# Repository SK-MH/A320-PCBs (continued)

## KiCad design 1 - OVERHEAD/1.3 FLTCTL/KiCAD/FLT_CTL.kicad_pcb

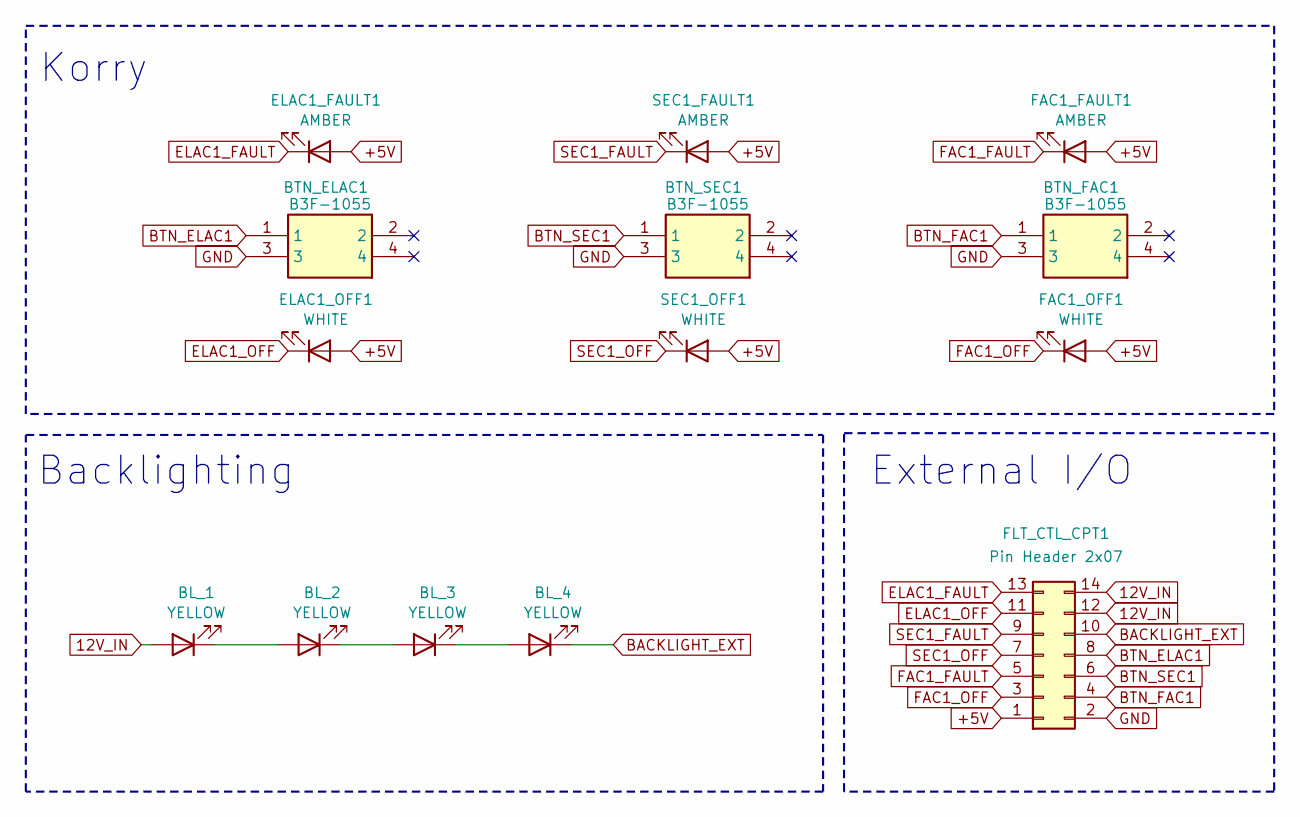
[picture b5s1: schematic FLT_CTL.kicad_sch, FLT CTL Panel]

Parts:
BL_1, BL_2, BL_3, BL_4: YELLOW; LED_D3.0mm
BTN_ELAC1: B3F-1055; B3F1000; Mouser Part Number 653-B3F-1055
BTN_FAC1: B3F-1055; B3F1000; Mouser Part Number 653-B3F-1055
BTN_SEC1: B3F-1055; B3F1000; Mouser Part Number 653-B3F-1055
ELAC1_FAULT1: AMBER; LED_D3.0mm
ELAC1_OFF1: WHITE; LED_D3.0mm
FAC1_FAULT1: AMBER; LED_D3.0mm
FAC1_OFF1: WHITE; LED_D3.0mm
FLT_CTL_CPT1: Pin Header 2x07; IDC-Header_2x07_P2.54mm_Vertical
SEC1_FAULT1: AMBER; LED_D3.0mm
SEC1_OFF1: WHITE; LED_D3.0mm

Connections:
12V_IN: BL_1.2 (A), FLT_CTL_CPT1.12, FLT_CTL_CPT1.14
+5V: ELAC1_FAULT1.2 (A), ELAC1_OFF1.2 (A), FAC1_FAULT1.2 (A), FAC1_OFF1.2 (A), FLT_CTL_CPT1.1, SEC1_FAULT1.2 (A), SEC1_OFF1.2 (A)
BACKLIGHT_EXT: BL_4.1 (K), FLT_CTL_CPT1.10
BTN_ELAC1: BTN_ELAC1.1, FLT_CTL_CPT1.8
BTN_FAC1: BTN_FAC1.1, FLT_CTL_CPT1.4
BTN_SEC1: BTN_SEC1.1, FLT_CTL_CPT1.6
ELAC1_FAULT: ELAC1_FAULT1.1 (K), FLT_CTL_CPT1.13
ELAC1_OFF: ELAC1_OFF1.1 (K), FLT_CTL_CPT1.11
FAC1_FAULT: FAC1_FAULT1.1 (K), FLT_CTL_CPT1.5
FAC1_OFF: FAC1_OFF1.1 (K), FLT_CTL_CPT1.3
GND: BTN_ELAC1.3, BTN_FAC1.3, BTN_SEC1.3, FLT_CTL_CPT1.2
unnamed: BL_1.1 (K), BL_2.2 (A)
unnamed: BL_2.1 (K), BL_3.2 (A)
unnamed: BL_3.1 (K), BL_4.2 (A)
SEC1_FAULT: FLT_CTL_CPT1.9, SEC1_FAULT1.1 (K)
SEC1_OFF: FLT_CTL_CPT1.7, SEC1_OFF1.1 (K)

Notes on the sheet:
Backlighting
External I/O
Korry

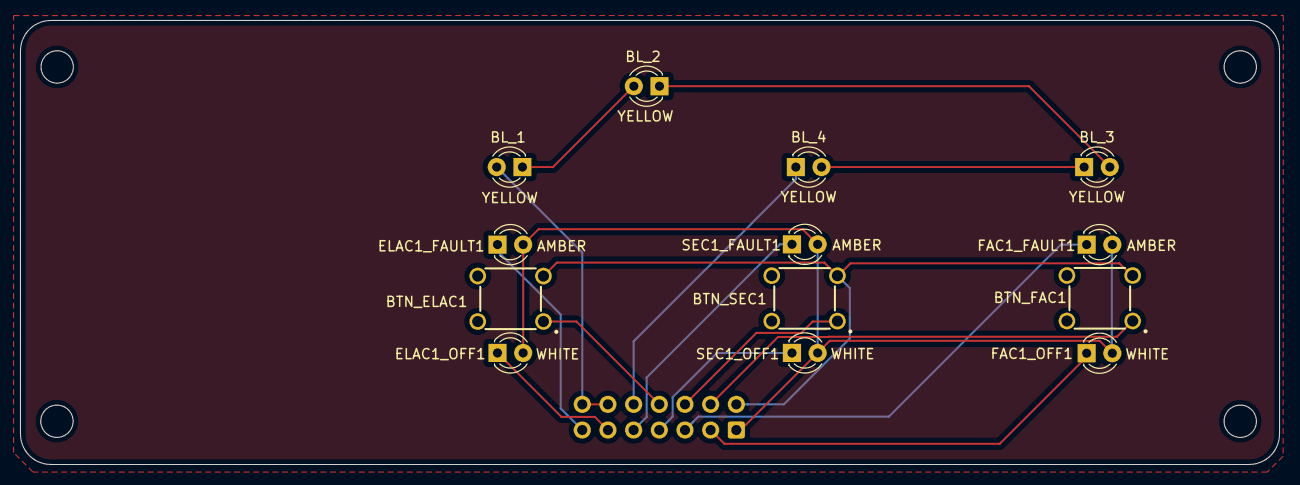
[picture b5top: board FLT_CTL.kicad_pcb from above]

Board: 2 copper layers, 124.6 x 43.9 mm, 14 parts (1 on the bottom side), 16 nets.

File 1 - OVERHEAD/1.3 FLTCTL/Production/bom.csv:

Designator,Footprint,Quantity,Value,LCSC Part #
"BL_1, BL_2, BL_3, BL_4",LED_D3.0mm,4,YELLOW,
"BTN_ELAC1, BTN_FAC1, BTN_SEC1",B3F1000,3,B3F-1055,
"ELAC1_FAULT1, FAC1_FAULT1, SEC1_FAULT1",LED_D3.0mm,3,AMBER,
"ELAC1_OFF1, FAC1_OFF1, SEC1_OFF1",LED_D3.0mm,3,WHITE,
FLT_CTL_CPT1,IDC-Header_2x07_P2.54mm_Vertical,1,Pin Header 2x07,

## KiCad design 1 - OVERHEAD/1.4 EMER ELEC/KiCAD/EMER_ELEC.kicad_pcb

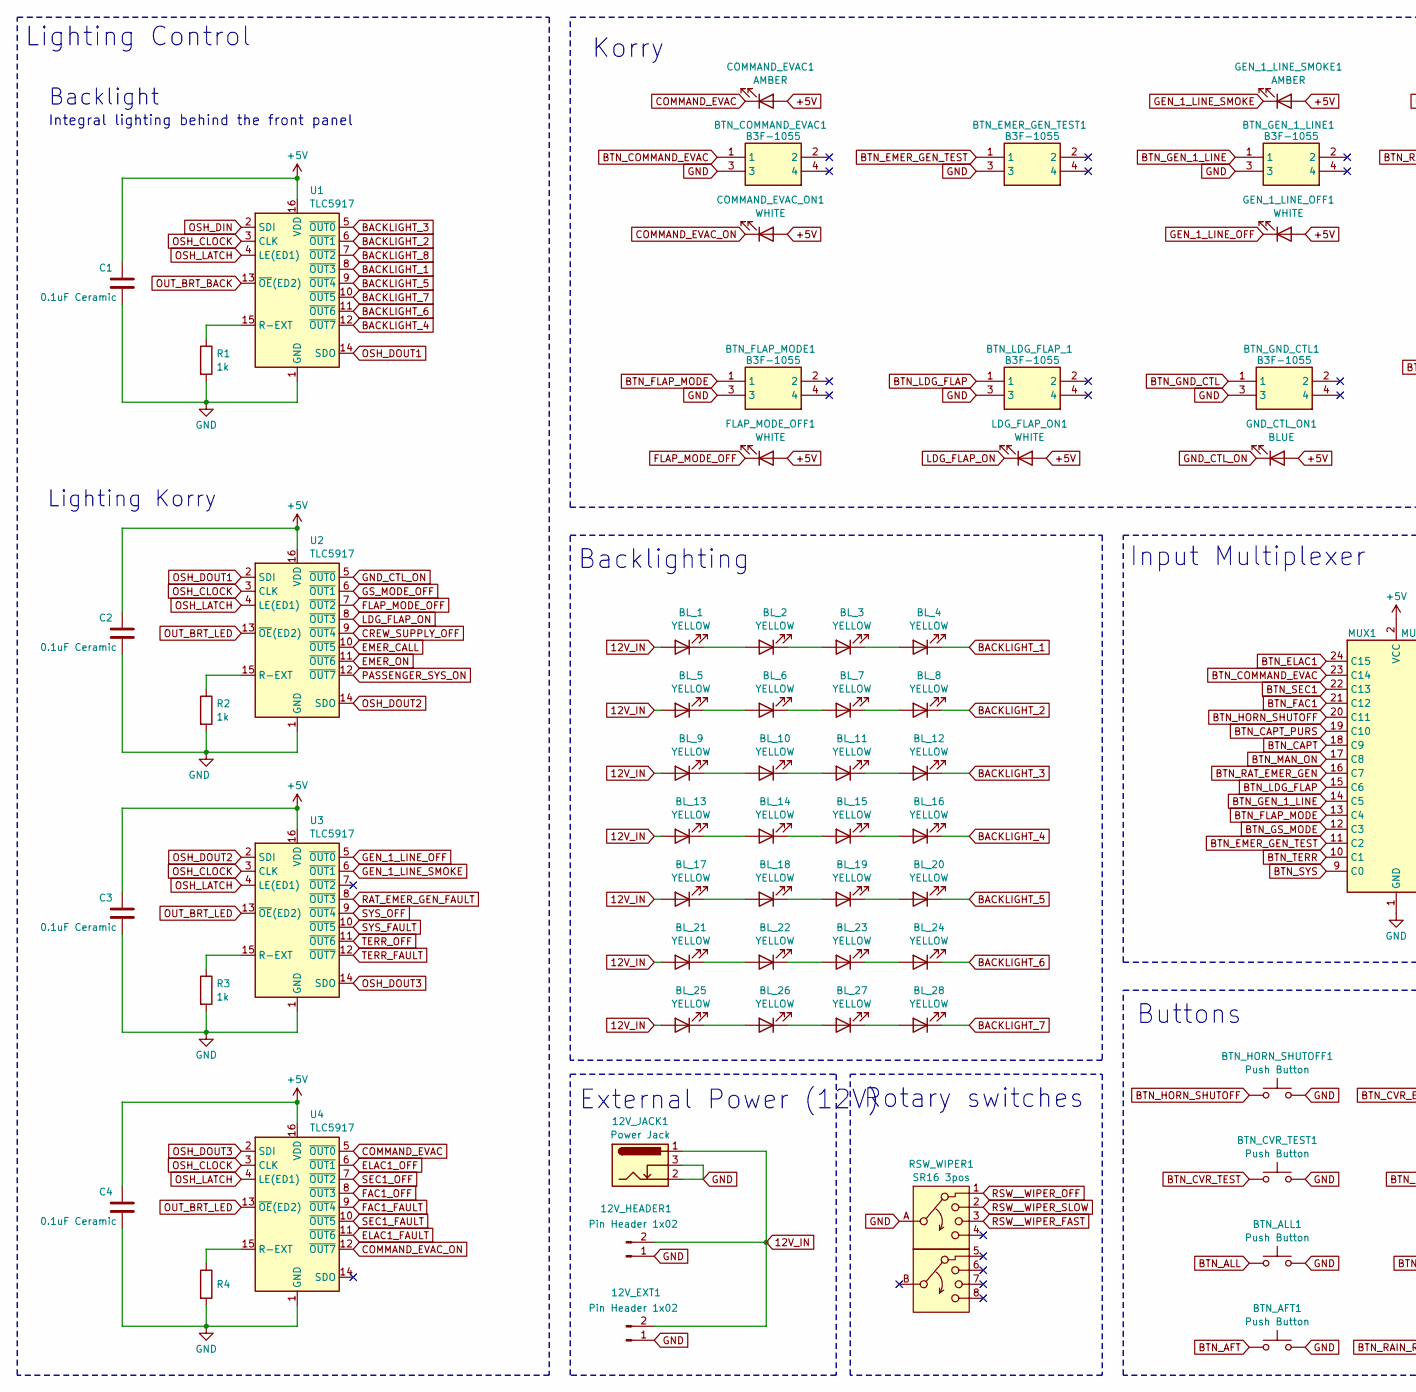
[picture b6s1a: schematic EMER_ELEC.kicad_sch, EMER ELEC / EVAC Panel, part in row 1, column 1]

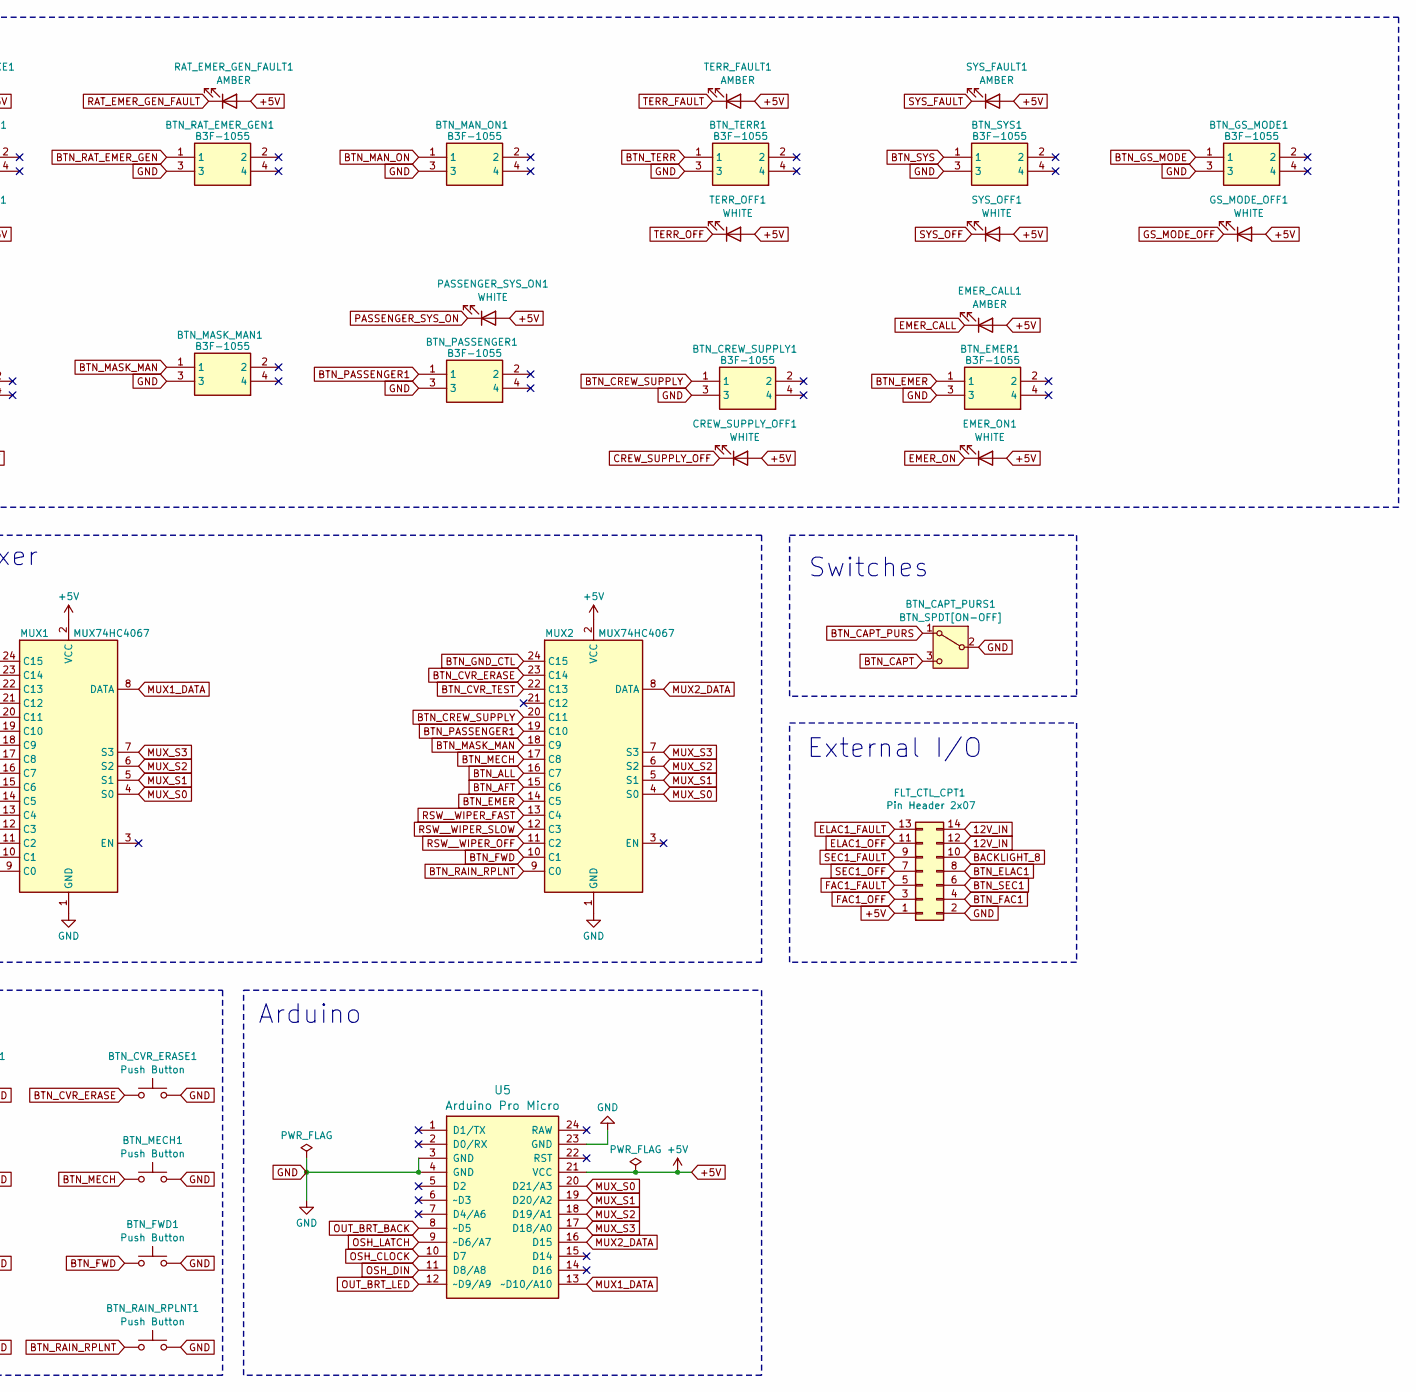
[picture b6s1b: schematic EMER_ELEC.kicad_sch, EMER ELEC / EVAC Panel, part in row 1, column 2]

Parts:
12V_EXT1, 12V_HEADER1: Pin Header 1x02; JST_EH_B2B-EH-A_1x02_P2.50mm_Vertical
12V_JACK1: Power Jack; BarrelJack_Horizontal
BL_1, BL_2, BL_3, BL_4, BL_5, BL_6, BL_7, BL_8, BL_9, BL_10, BL_11, BL_12, BL_13, BL_14, BL_15, BL_16, BL_17, BL_18, BL_19, BL_20, BL_21, BL_22, BL_23, BL_24, BL_25, BL_26, BL_27, BL_28: YELLOW; LED_D3.0mm
BTN_AFT1: Push Button; SW-Push
BTN_ALL1: Push Button; SW-Push
BTN_CAPT_PURS1: BTN_SPDT[ON-OFF]; T80-Z1
BTN_COMMAND_EVAC1: B3F-1055; B3F1000; Mouser Part Number 653-B3F-1055
BTN_CREW_SUPPLY1: B3F-1055; B3F1000; Mouser Part Number 653-B3F-1055
BTN_CVR_ERASE1: Push Button; SW-Push
BTN_CVR_TEST1: Push Button; SW-Push
BTN_EMER1: B3F-1055; B3F1000; Mouser Part Number 653-B3F-1055
BTN_EMER_GEN_TEST1: B3F-1055; B3F1000; Mouser Part Number 653-B3F-1055
BTN_FLAP_MODE1: B3F-1055; B3F1000; Mouser Part Number 653-B3F-1055
BTN_FWD1: Push Button; SW-Push
BTN_GEN_1_LINE1: B3F-1055; B3F1000; Mouser Part Number 653-B3F-1055
BTN_GND_CTL1: B3F-1055; B3F1000; Mouser Part Number 653-B3F-1055
BTN_GS_MODE1: B3F-1055; B3F1000; Mouser Part Number 653-B3F-1055
BTN_HORN_SHUTOFF1: Push Button; SW-Push
BTN_LDG_FLAP_1: B3F-1055; B3F1000; Mouser Part Number 653-B3F-1055
BTN_MAN_ON1: B3F-1055; B3F1000; Mouser Part Number 653-B3F-1055
BTN_MASK_MAN1: B3F-1055; B3F1000; Mouser Part Number 653-B3F-1055
BTN_MECH1: Push Button; SW-Push
BTN_PASSENGER1: B3F-1055; B3F1000; Mouser Part Number 653-B3F-1055
BTN_RAIN_RPLNT1: Push Button; SW-Push
BTN_RAT_EMER_GEN1: B3F-1055; B3F1000; Mouser Part Number 653-B3F-1055
BTN_SYS1: B3F-1055; B3F1000; Mouser Part Number 653-B3F-1055
BTN_TERR1: B3F-1055; B3F1000; Mouser Part Number 653-B3F-1055
C1, C2, C3, C4: 0.1uF Ceramic; C_Disc_D3.0mm_W1.6mm_P2.50mm
COMMAND_EVAC1: AMBER; LED_D3.0mm
COMMAND_EVAC_ON1: WHITE; LED_D3.0mm
CREW_SUPPLY_OFF1: WHITE; LED_D3.0mm
EMER_CALL1: AMBER; LED_D3.0mm
EMER_ON1: WHITE; LED_D3.0mm
FLAP_MODE_OFF1: WHITE; LED_D3.0mm
FLT_CTL_CPT1: Pin Header 2x07; IDC-Header_2x07_P2.54mm_Vertical
GEN_1_LINE_OFF1: WHITE; LED_D3.0mm
GEN_1_LINE_SMOKE1: AMBER; LED_D3.0mm
GND_CTL_ON1: BLUE; LED_D3.0mm
GS_MODE_OFF1: WHITE; LED_D3.0mm
LDG_FLAP_ON1: WHITE; LED_D3.0mm
MUX1, MUX2: MUX74HC4067
PASSENGER_SYS_ON1: WHITE; LED_D3.0mm
R1, R2, R3, R4: 1k; R_Axial_DIN0204_L3.6mm_D1.6mm_P7.62mm_Horizontal
RAT_EMER_GEN_FAULT1: AMBER; LED_D3.0mm
RSW_WIPER1: SR16 3pos; SR16-AB
SYS_FAULT1: AMBER; LED_D3.0mm
SYS_OFF1: WHITE; LED_D3.0mm
TERR_FAULT1: AMBER; LED_D3.0mm
TERR_OFF1: WHITE; LED_D3.0mm
U1, U2, U3, U4: TLC5917; DIP-16_W7.62mm
U5: Arduino Pro Micro; Sparkfun_Pro_Micro

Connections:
12V_IN: 12V_EXT1.2, 12V_HEADER1.2, 12V_JACK1.1, BL_1.2 (A), BL_5.2 (A), BL_9.2 (A), BL_13.2 (A), BL_17.2 (A), BL_21.2 (A), BL_25.2 (A), FLT_CTL_CPT1.12, FLT_CTL_CPT1.14
+5V: C1.1, C2.1, C3.1, C4.1, COMMAND_EVAC1.2 (A), COMMAND_EVAC_ON1.2 (A), CREW_SUPPLY_OFF1.2 (A), EMER_CALL1.2 (A), EMER_ON1.2 (A), FLAP_MODE_OFF1.2 (A), FLT_CTL_CPT1.1, GEN_1_LINE_OFF1.2 (A), GEN_1_LINE_SMOKE1.2 (A), GND_CTL_ON1.2 (A), GS_MODE_OFF1.2 (A), LDG_FLAP_ON1.2 (A), MUX1.2 (VCC), MUX2.2 (VCC), PASSENGER_SYS_ON1.2 (A), RAT_EMER_GEN_FAULT1.2 (A), SYS_FAULT1.2 (A), SYS_OFF1.2 (A), TERR_FAULT1.2 (A), TERR_OFF1.2 (A), U1.16 (VDD), U2.16 (VDD), U3.16 (VDD), U4.16 (VDD), U5.21 (VCC)
BACKLIGHT_1: BL_4.1 (K), U1.8 (~OUT3)
BACKLIGHT_2: BL_8.1 (K), U1.6 (~OUT1)
BACKLIGHT_3: BL_12.1 (K), U1.5 (~OUT0)
BACKLIGHT_4: BL_16.1 (K), U1.12 (~OUT7)
BACKLIGHT_5: BL_20.1 (K), U1.9 (~OUT4)
BACKLIGHT_6: BL_24.1 (K), U1.11 (~OUT6)
BACKLIGHT_7: BL_28.1 (K), U1.10 (~OUT5)
BACKLIGHT_8: FLT_CTL_CPT1.10, U1.7 (~OUT2)
BTN_AFT: BTN_AFT1.1, MUX2.15 (C6)
BTN_ALL: BTN_ALL1.1, MUX2.16 (C7)
BTN_CAPT: BTN_CAPT_PURS1.3 (C), MUX1.18 (C9)
BTN_CAPT_PURS: BTN_CAPT_PURS1.1 (A), MUX1.19 (C10)
BTN_COMMAND_EVAC: BTN_COMMAND_EVAC1.1, MUX1.23 (C14)
BTN_CREW_SUPPLY: BTN_CREW_SUPPLY1.1, MUX2.20 (C11)
BTN_CVR_ERASE: BTN_CVR_ERASE1.1, MUX2.23 (C14)
BTN_CVR_TEST: BTN_CVR_TEST1.1, MUX2.22 (C13)
BTN_ELAC1: FLT_CTL_CPT1.8, MUX1.24 (C15)
BTN_EMER: BTN_EMER1.1, MUX2.14 (C5)
BTN_EMER_GEN_TEST: BTN_EMER_GEN_TEST1.1, MUX1.11 (C2)
BTN_FAC1: FLT_CTL_CPT1.4, MUX1.21 (C12)
BTN_FLAP_MODE: BTN_FLAP_MODE1.1, MUX1.13 (C4)
BTN_FWD: BTN_FWD1.1, MUX2.10 (C1)
BTN_GEN_1_LINE: BTN_GEN_1_LINE1.1, MUX1.14 (C5)
BTN_GND_CTL: BTN_GND_CTL1.1, MUX2.24 (C15)
BTN_GS_MODE: BTN_GS_MODE1.1, MUX1.12 (C3)
BTN_HORN_SHUTOFF: BTN_HORN_SHUTOFF1.1, MUX1.20 (C11)
BTN_LDG_FLAP: BTN_LDG_FLAP_1.1, MUX1.15 (C6)
BTN_MAN_ON: BTN_MAN_ON1.1, MUX1.17 (C8)
BTN_MASK_MAN: BTN_MASK_MAN1.1, MUX2.18 (C9)
BTN_MECH: BTN_MECH1.1, MUX2.17 (C8)
BTN_PASSENGER1: BTN_PASSENGER1.1, MUX2.19 (C10)
BTN_RAIN_RPLNT: BTN_RAIN_RPLNT1.1, MUX2.9 (C0)
BTN_RAT_EMER_GEN: BTN_RAT_EMER_GEN1.1, MUX1.16 (C7)
BTN_SEC1: FLT_CTL_CPT1.6, MUX1.22 (C13)
BTN_SYS: BTN_SYS1.1, MUX1.9 (C0)
BTN_TERR: BTN_TERR1.1, MUX1.10 (C1)
COMMAND_EVAC: COMMAND_EVAC1.1 (K), U4.5 (~OUT0)
COMMAND_EVAC_ON: COMMAND_EVAC_ON1.1 (K), U4.12 (~OUT7)
CREW_SUPPLY_OFF: CREW_SUPPLY_OFF1.1 (K), U2.9 (~OUT4)
ELAC1_FAULT: FLT_CTL_CPT1.13, U4.11 (~OUT6)
ELAC1_OFF: FLT_CTL_CPT1.11, U4.6 (~OUT1)
EMER_CALL: EMER_CALL1.1 (K), U2.10 (~OUT5)
EMER_ON: EMER_ON1.1 (K), U2.11 (~OUT6)
FAC1_FAULT: FLT_CTL_CPT1.5, U4.9 (~OUT4)
FAC1_OFF: FLT_CTL_CPT1.3, U4.8 (~OUT3)
FLAP_MODE_OFF: FLAP_MODE_OFF1.1 (K), U2.7 (~OUT2)
GEN_1_LINE_OFF: GEN_1_LINE_OFF1.1 (K), U3.5 (~OUT0)
GEN_1_LINE_SMOKE: GEN_1_LINE_SMOKE1.1 (K), U3.6 (~OUT1)
GND: 12V_EXT1.1, 12V_HEADER1.1, 12V_JACK1.2, 12V_JACK1.3, BTN_AFT1.2, BTN_ALL1.2, BTN_CAPT_PURS1.2 (B), BTN_COMMAND_EVAC1.3, BTN_CREW_SUPPLY1.3, BTN_CVR_ERASE1.2, BTN_CVR_TEST1.2, BTN_EMER1.3, BTN_EMER_GEN_TEST1.3, BTN_FLAP_MODE1.3, BTN_FWD1.2, BTN_GEN_1_LINE1.3, BTN_GND_CTL1.3, BTN_GS_MODE1.3, BTN_HORN_SHUTOFF1.2, BTN_LDG_FLAP_1.3, BTN_MAN_ON1.3, BTN_MASK_MAN1.3, BTN_MECH1.2, BTN_PASSENGER1.3, BTN_RAIN_RPLNT1.2, BTN_RAT_EMER_GEN1.3, BTN_SYS1.3, BTN_TERR1.3, C1.2, C2.2, C3.2, C4.2, FLT_CTL_CPT1.2, MUX1.1 (GND), MUX2.1 (GND), R1.2, R2.2, R3.2, R4.2, RSW_WIPER1.A, U1.1 (GND), U2.1 (GND), U3.1 (GND), U4.1 (GND), U5.3 (GND), U5.4 (GND), U5.23 (GND)
GND_CTL_ON: GND_CTL_ON1.1 (K), U2.5 (~OUT0)
GS_MODE_OFF: GS_MODE_OFF1.1 (K), U2.6 (~OUT1)
LDG_FLAP_ON: LDG_FLAP_ON1.1 (K), U2.8 (~OUT3)
MUX1_DATA: MUX1.8 (DATA), U5.13 (~D10/A10)
MUX2_DATA: MUX2.8 (DATA), U5.16 (D15)
MUX_S0: MUX1.4 (S0), MUX2.4 (S0), U5.20 (D21/A3)
MUX_S1: MUX1.5 (S1), MUX2.5 (S1), U5.19 (D20/A2)
MUX_S2: MUX1.6 (S2), MUX2.6 (S2), U5.18 (D19/A1)
MUX_S3: MUX1.7 (S3), MUX2.7 (S3), U5.17 (D18/A0)
unnamed: BL_1.1 (K), BL_2.2 (A)
unnamed: BL_2.1 (K), BL_3.2 (A)
unnamed: BL_3.1 (K), BL_4.2 (A)
unnamed: BL_5.1 (K), BL_6.2 (A)
unnamed: BL_6.1 (K), BL_7.2 (A)
unnamed: BL_7.1 (K), BL_8.2 (A)
unnamed: BL_9.1 (K), BL_10.2 (A)
unnamed: BL_10.1 (K), BL_11.2 (A)
unnamed: BL_11.1 (K), BL_12.2 (A)
unnamed: BL_13.1 (K), BL_14.2 (A)
unnamed: BL_14.1 (K), BL_15.2 (A)
unnamed: BL_15.1 (K), BL_16.2 (A)
unnamed: BL_17.1 (K), BL_18.2 (A)
unnamed: BL_18.1 (K), BL_19.2 (A)
unnamed: BL_19.1 (K), BL_20.2 (A)
unnamed: BL_21.1 (K), BL_22.2 (A)
unnamed: BL_22.1 (K), BL_23.2 (A)
unnamed: BL_23.1 (K), BL_24.2 (A)
unnamed: BL_25.1 (K), BL_26.2 (A)
unnamed: BL_26.1 (K), BL_27.2 (A)
unnamed: BL_27.1 (K), BL_28.2 (A)
unnamed: R1.1, U1.15 (R-EXT)
unnamed: R2.1, U2.15 (R-EXT)
unnamed: R3.1, U3.15 (R-EXT)
unnamed: R4.1, U4.15 (R-EXT)
OSH_CLOCK: U1.3 (CLK), U2.3 (CLK), U3.3 (CLK), U4.3 (CLK), U5.10 (D7)
OSH_DIN: U1.2 (SDI), U5.11 (D8/A8)
OSH_DOUT1: U1.14 (SDO), U2.2 (SDI)
OSH_DOUT2: U2.14 (SDO), U3.2 (SDI)
OSH_DOUT3: U3.14 (SDO), U4.2 (SDI)
OSH_LATCH: U1.4 (LE(ED1)), U2.4 (LE(ED1)), U3.4 (LE(ED1)), U4.4 (LE(ED1)), U5.9 (~D6/A7)
OUT_BRT_BACK: U1.13 (~OE(ED2)), U5.8 (~D5)
OUT_BRT_LED: U2.13 (~OE(ED2)), U3.13 (~OE(ED2)), U4.13 (~OE(ED2)), U5.12 (~D9/A9)
PASSENGER_SYS_ON: PASSENGER_SYS_ON1.1 (K), U2.12 (~OUT7)
RAT_EMER_GEN_FAULT: RAT_EMER_GEN_FAULT1.1 (K), U3.8 (~OUT3)
RSW__WIPER_FAST: MUX2.13 (C4), RSW_WIPER1.3
RSW__WIPER_OFF: MUX2.11 (C2), RSW_WIPER1.1
RSW__WIPER_SLOW: MUX2.12 (C3), RSW_WIPER1.2
SEC1_FAULT: FLT_CTL_CPT1.9, U4.10 (~OUT5)
SEC1_OFF: FLT_CTL_CPT1.7, U4.7 (~OUT2)
SYS_FAULT: SYS_FAULT1.1 (K), U3.10 (~OUT5)
SYS_OFF: SYS_OFF1.1 (K), U3.9 (~OUT4)
TERR_FAULT: TERR_FAULT1.1 (K), U3.12 (~OUT7)
TERR_OFF: TERR_OFF1.1 (K), U3.11 (~OUT6)

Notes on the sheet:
Backlighting
Arduino
Rotary switches
Switches
External I/O
Korry
Input Multiplexer
Buttons
External Power (12V)
Lighting Korry
Lighting Control
Integral lighting behind the front panel
Backlight

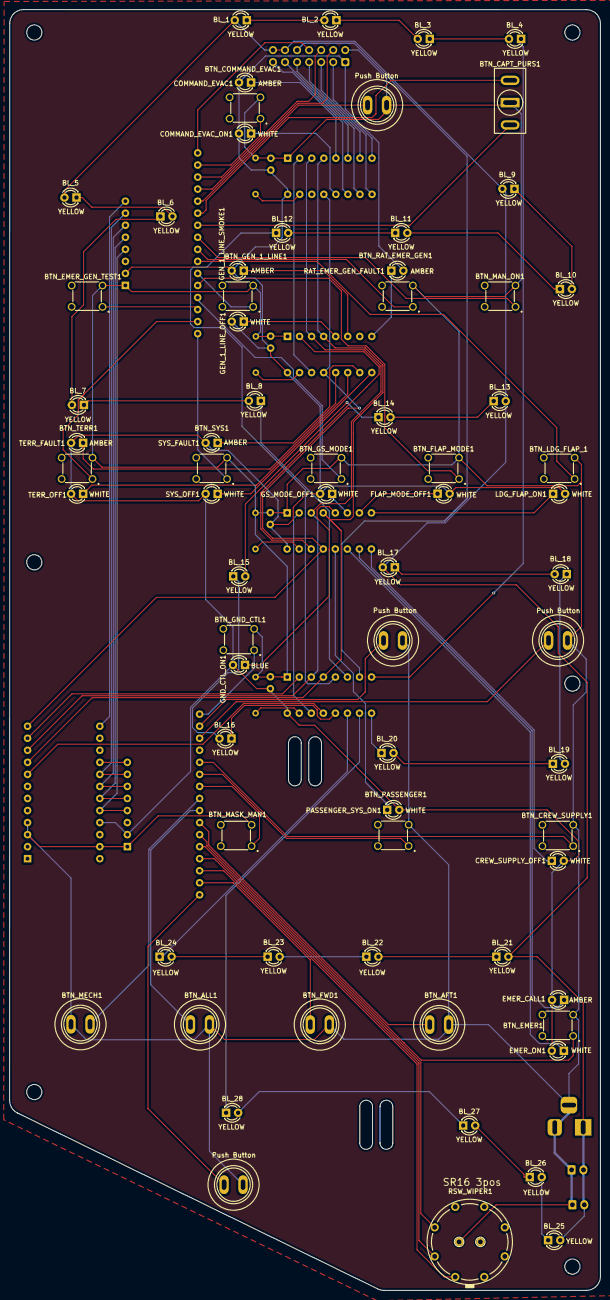
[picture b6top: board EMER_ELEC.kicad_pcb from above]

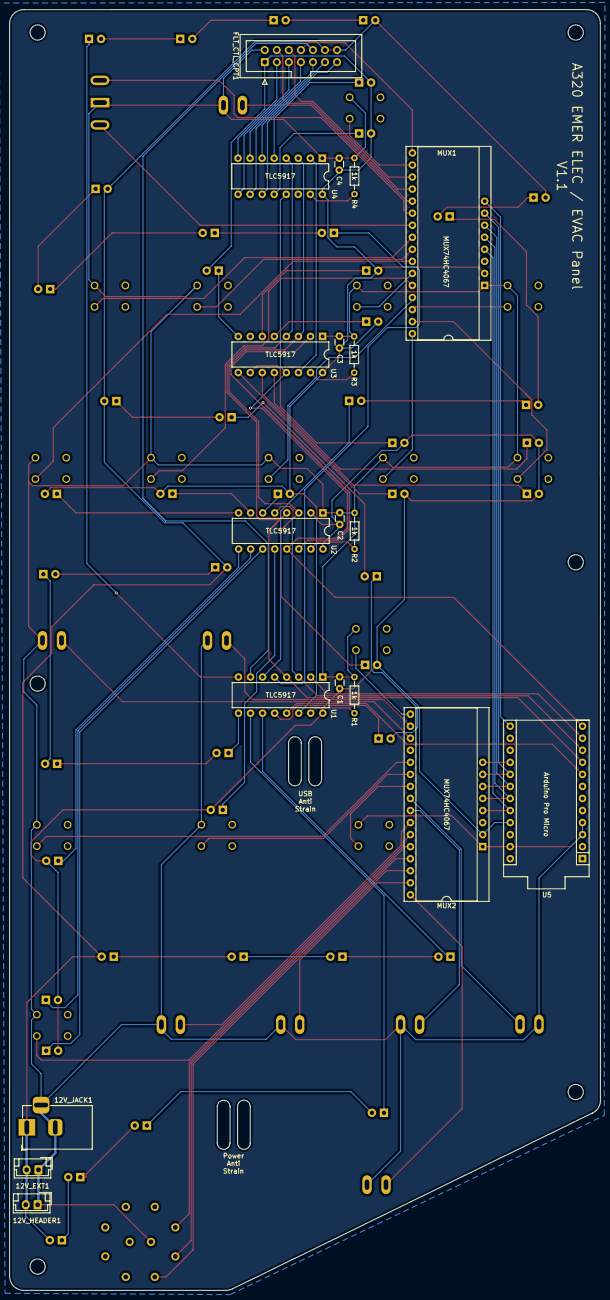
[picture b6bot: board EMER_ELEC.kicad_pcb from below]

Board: 2 copper layers, 124.6 x 270.1 mm, 89 parts (19 on the bottom side), 104 nets.

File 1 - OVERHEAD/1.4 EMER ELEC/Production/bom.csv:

Designator,Footprint,Quantity,Value,LCSC Part #
"12V_EXT1, 12V_HEADER1",JST_EH_B2B-EH-A_1x02_P2.50mm_Vertical,2,Pin Header 1x02,
12V_JACK1,BarrelJack_Horizontal,1,Power Jack,
"BL_1, BL_10, BL_11, BL_12, BL_13, BL_14, BL_15, BL_16, BL_17, BL_18, BL_19, BL_2, BL_20, BL_21, BL_22, BL_23, BL_24, BL_25, BL_26, BL_27, BL_28, BL_3, BL_4, BL_5, BL_6, BL_7, BL_8, BL_9",LED_D3.0mm,28,YELLOW,
"BTN_AFT1, BTN_ALL1, BTN_CVR_ERASE1, BTN_CVR_TEST1, BTN_FWD1, BTN_HORN_SHUTOFF1, BTN_MECH1, BTN_RAIN_RPLNT1",SW-Push,8,Push Button,
BTN_CAPT_PURS1,T80-Z1,1,BTN_SPDT[ON-OFF],
"BTN_COMMAND_EVAC1, BTN_CREW_SUPPLY1, BTN_EMER1, BTN_EMER_GEN_TEST1, BTN_FLAP_MODE1, BTN_GEN_1_LINE1, BTN_GND_CTL1, BTN_GS_MODE1, BTN_LDG_FLAP_1, BTN_MAN_ON1, BTN_MASK_MAN1, BTN_PASSENGER1, BTN_RAT_EMER_GEN1, BTN_SYS1, BTN_TERR1",B3F1000,15,B3F-1055,
"C1, C2, C3, C4",C_Disc_D3.0mm_W1.6mm_P2.50mm,4,0.1uF Ceramic,
"COMMAND_EVAC1, EMER_CALL1, GEN_1_LINE_SMOKE1, RAT_EMER_GEN_FAULT1, SYS_FAULT1, TERR_FAULT1",LED_D3.0mm,6,AMBER,
"COMMAND_EVAC_ON1, CREW_SUPPLY_OFF1, EMER_ON1, FLAP_MODE_OFF1, GEN_1_LINE_OFF1, GS_MODE_OFF1, LDG_FLAP_ON1, PASSENGER_SYS_ON1, SYS_OFF1, TERR_OFF1",LED_D3.0mm,10,WHITE,
FLT_CTL_CPT1,IDC-Header_2x07_P2.54mm_Vertical,1,Pin Header 2x07,
GND_CTL_ON1,LED_D3.0mm,1,BLUE,
"MUX1, MUX2",MUX74HC4067,2,MUX74HC4067,
"R1, R2, R3, R4",R_Axial_DIN0204_L3.6mm_D1.6mm_P7.62mm_Horizontal,4,1k,
RSW_WIPER1,SR16-AB,1,SR16 3pos,
"U1, U2, U3, U4",DIP-16_W7.62mm,4,TLC5917,
U5,Sparkfun_Pro_Micro,1,Arduino Pro Micro,

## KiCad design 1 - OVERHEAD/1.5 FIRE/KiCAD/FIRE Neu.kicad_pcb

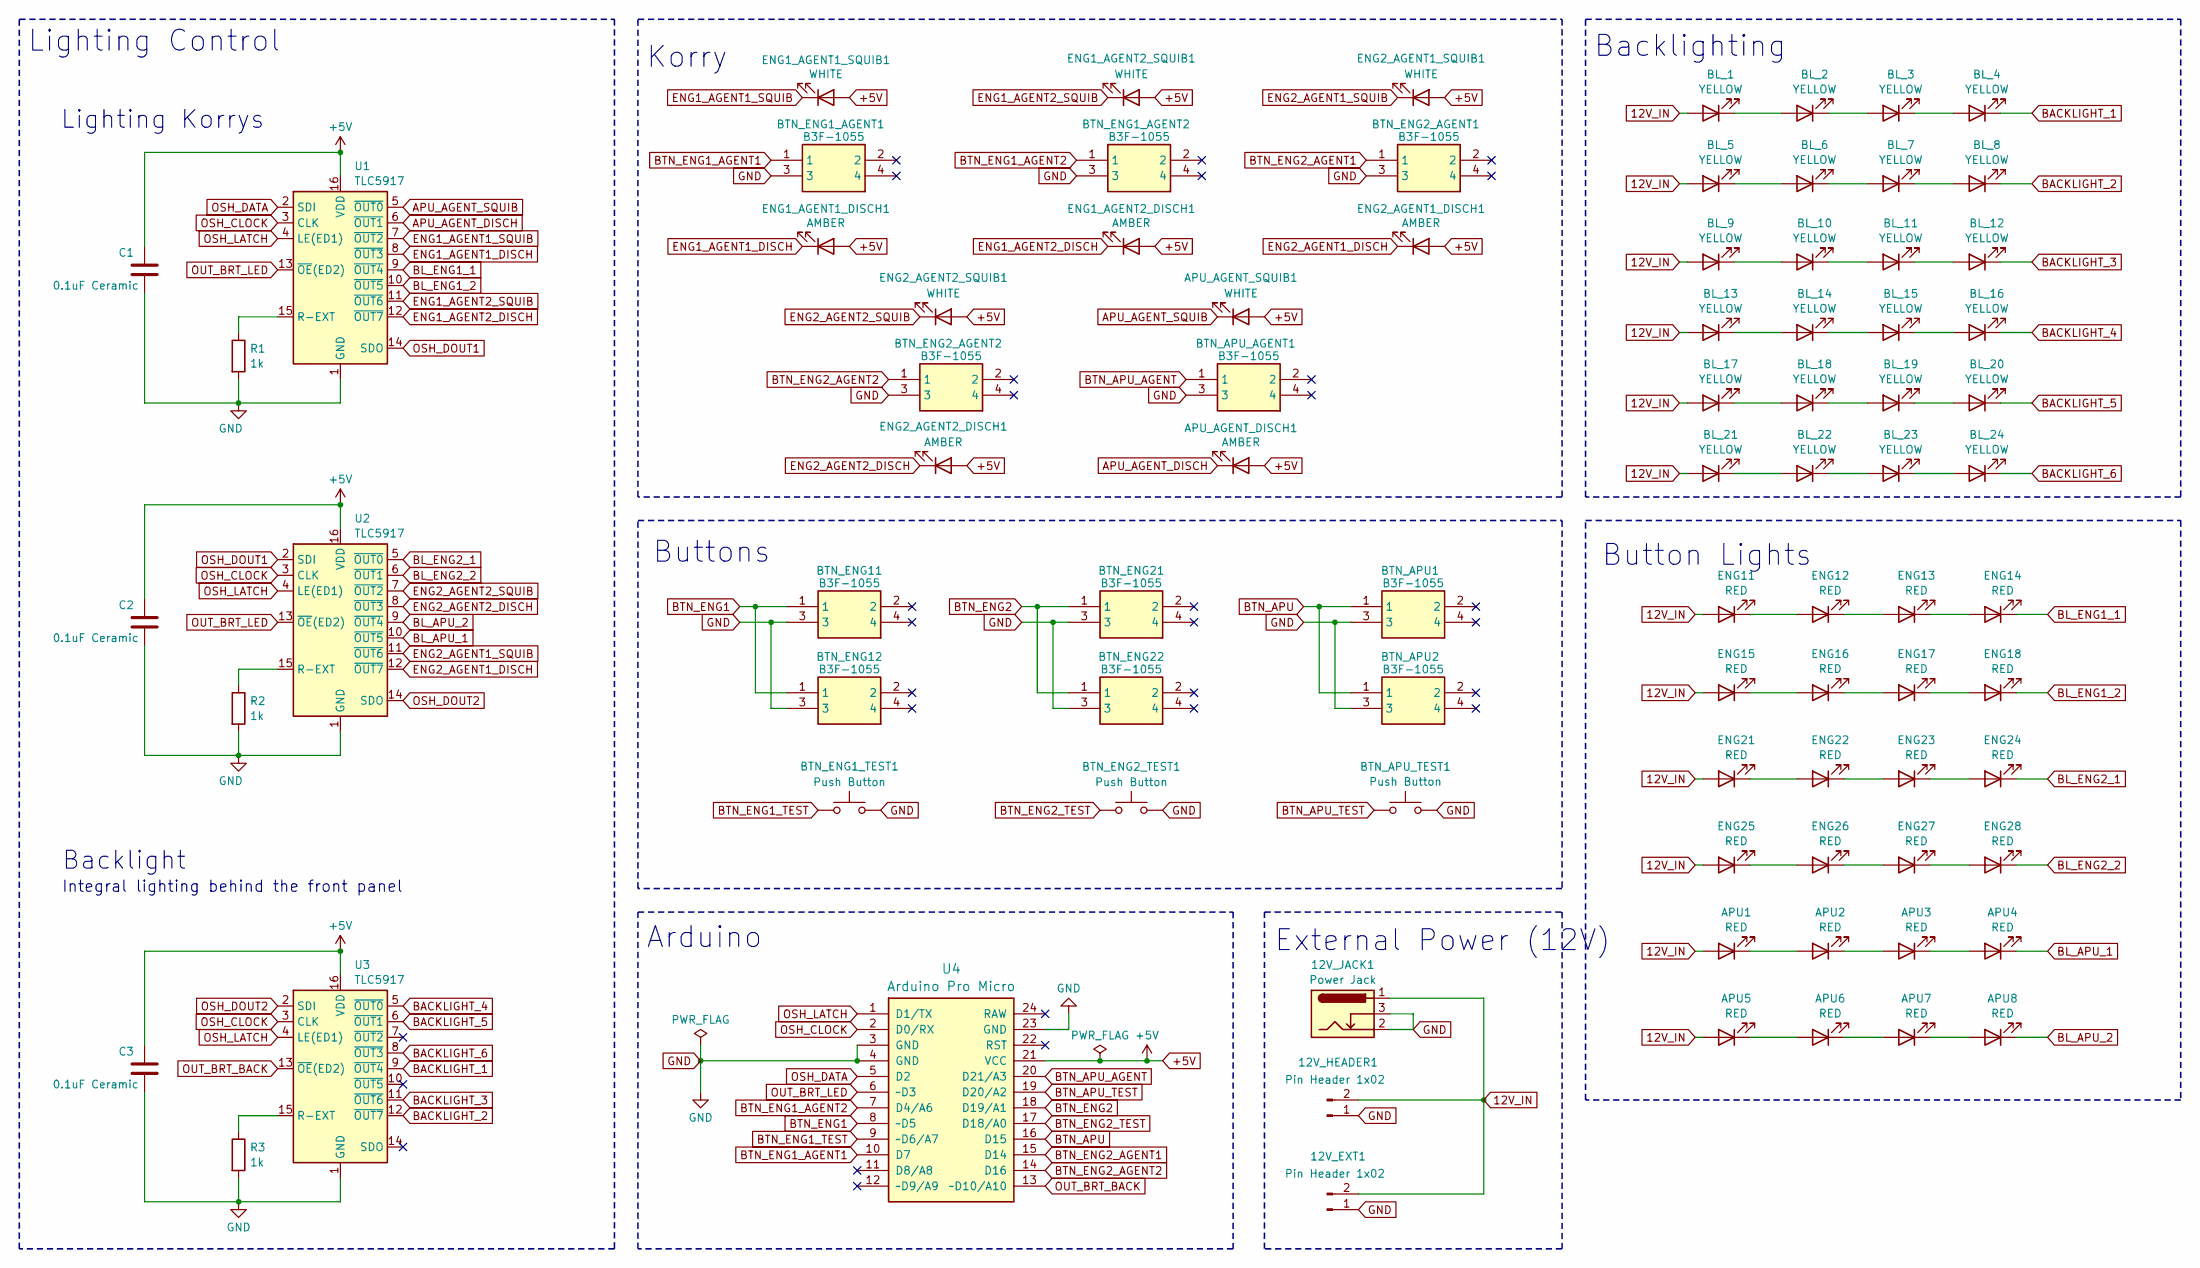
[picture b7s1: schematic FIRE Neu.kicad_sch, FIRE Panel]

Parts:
12V_EXT1, 12V_HEADER1: Pin Header 1x02; JST_EH_B2B-EH-A_1x02_P2.50mm_Vertical
12V_JACK1: Power Jack; BarrelJack_Horizontal
APU1, APU2, APU3, APU4, APU5, APU6, APU7, APU8: RED; LED_D3.0mm
APU_AGENT_DISCH1: AMBER; LED_D3.0mm
APU_AGENT_SQUIB1: WHITE; LED_D3.0mm
BL_1, BL_2, BL_3, BL_4, BL_5, BL_6, BL_7, BL_8, BL_9, BL_10, BL_11, BL_12, BL_13, BL_14, BL_15, BL_16, BL_17, BL_18, BL_19, BL_20, BL_21, BL_22, BL_23, BL_24: YELLOW; LED_D3.0mm
BTN_APU1, BTN_APU2: B3F-1055; B3F1000; Mouser Part Number 653-B3F-1055
BTN_APU_AGENT1: B3F-1055; B3F1000; Mouser Part Number 653-B3F-1055
BTN_APU_TEST1: Push Button; SW-Push
BTN_ENG1_AGENT1, BTN_ENG1_AGENT2, BTN_ENG2_AGENT1, BTN_ENG2_AGENT2, BTN_ENG11, BTN_ENG12, BTN_ENG21, BTN_ENG22: B3F-1055; B3F1000; Mouser Part Number 653-B3F-1055
BTN_ENG1_TEST1, BTN_ENG2_TEST1: Push Button; SW-Push
C1, C2, C3: 0.1uF Ceramic; C_Disc_D3.0mm_W1.6mm_P2.50mm
ENG1_AGENT1_DISCH1, ENG1_AGENT2_DISCH1, ENG2_AGENT1_DISCH1, ENG2_AGENT2_DISCH1: AMBER; LED_D3.0mm
ENG1_AGENT1_SQUIB1, ENG1_AGENT2_SQUIB1, ENG2_AGENT1_SQUIB1, ENG2_AGENT2_SQUIB1: WHITE; LED_D3.0mm
ENG11, ENG12, ENG13, ENG14, ENG15, ENG16, ENG17, ENG18, ENG21, ENG22, ENG23, ENG24, ENG25, ENG26, ENG27, ENG28: RED; LED_D3.0mm
R1, R2, R3: 1k; R_Axial_DIN0204_L3.6mm_D1.6mm_P5.08mm_Horizontal
U1, U2, U3: TLC5917; DIP-16_W7.62mm
U4: Arduino Pro Micro; Sparkfun_Pro_Micro

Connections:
12V_IN: 12V_EXT1.2, 12V_HEADER1.2, 12V_JACK1.1, APU1.2 (A), APU5.2 (A), BL_1.2 (A), BL_5.2 (A), BL_9.2 (A), BL_13.2 (A), BL_17.2 (A), BL_21.2 (A), ENG11.2 (A), ENG15.2 (A), ENG21.2 (A), ENG25.2 (A)
+5V: APU_AGENT_DISCH1.2 (A), APU_AGENT_SQUIB1.2 (A), C1.1, C2.1, C3.1, ENG1_AGENT1_DISCH1.2 (A), ENG1_AGENT1_SQUIB1.2 (A), ENG1_AGENT2_DISCH1.2 (A), ENG1_AGENT2_SQUIB1.2 (A), ENG2_AGENT1_DISCH1.2 (A), ENG2_AGENT1_SQUIB1.2 (A), ENG2_AGENT2_DISCH1.2 (A), ENG2_AGENT2_SQUIB1.2 (A), U1.16 (VDD), U2.16 (VDD), U3.16 (VDD), U4.21 (VCC)
APU_AGENT_DISCH: APU_AGENT_DISCH1.1 (K), U1.6 (~OUT1)
APU_AGENT_SQUIB: APU_AGENT_SQUIB1.1 (K), U1.5 (~OUT0)
BACKLIGHT_1: BL_4.1 (K), U3.9 (~OUT4)
BACKLIGHT_2: BL_8.1 (K), U3.12 (~OUT7)
BACKLIGHT_3: BL_12.1 (K), U3.11 (~OUT6)
BACKLIGHT_4: BL_16.1 (K), U3.5 (~OUT0)
BACKLIGHT_5: BL_20.1 (K), U3.6 (~OUT1)
BACKLIGHT_6: BL_24.1 (K), U3.8 (~OUT3)
BL_APU_1: APU4.1 (K), U2.10 (~OUT5)
BL_APU_2: APU8.1 (K), U2.9 (~OUT4)
BL_ENG1_1: ENG14.1 (K), U1.9 (~OUT4)
BL_ENG1_2: ENG18.1 (K), U1.10 (~OUT5)
BL_ENG2_1: ENG24.1 (K), U2.5 (~OUT0)
BL_ENG2_2: ENG28.1 (K), U2.6 (~OUT1)
BTN_APU: BTN_APU1.1, BTN_APU2.1, U4.16 (D15)
BTN_APU_AGENT: BTN_APU_AGENT1.1, U4.20 (D21/A3)
BTN_APU_TEST: BTN_APU_TEST1.1, U4.19 (D20/A2)
BTN_ENG1: BTN_ENG11.1, BTN_ENG12.1, U4.8 (~D5)
BTN_ENG1_AGENT1: BTN_ENG1_AGENT1.1, U4.10 (D7)
BTN_ENG1_AGENT2: BTN_ENG1_AGENT2.1, U4.7 (D4/A6)
BTN_ENG1_TEST: BTN_ENG1_TEST1.1, U4.9 (~D6/A7)
BTN_ENG2: BTN_ENG21.1, BTN_ENG22.1, U4.18 (D19/A1)
BTN_ENG2_AGENT1: BTN_ENG2_AGENT1.1, U4.15 (D14)
BTN_ENG2_AGENT2: BTN_ENG2_AGENT2.1, U4.14 (D16)
BTN_ENG2_TEST: BTN_ENG2_TEST1.1, U4.17 (D18/A0)
ENG1_AGENT1_DISCH: ENG1_AGENT1_DISCH1.1 (K), U1.8 (~OUT3)
ENG1_AGENT1_SQUIB: ENG1_AGENT1_SQUIB1.1 (K), U1.7 (~OUT2)
ENG1_AGENT2_DISCH: ENG1_AGENT2_DISCH1.1 (K), U1.12 (~OUT7)
ENG1_AGENT2_SQUIB: ENG1_AGENT2_SQUIB1.1 (K), U1.11 (~OUT6)
ENG2_AGENT1_DISCH: ENG2_AGENT1_DISCH1.1 (K), U2.12 (~OUT7)
ENG2_AGENT1_SQUIB: ENG2_AGENT1_SQUIB1.1 (K), U2.11 (~OUT6)
ENG2_AGENT2_DISCH: ENG2_AGENT2_DISCH1.1 (K), U2.8 (~OUT3)
ENG2_AGENT2_SQUIB: ENG2_AGENT2_SQUIB1.1 (K), U2.7 (~OUT2)
GND: 12V_EXT1.1, 12V_HEADER1.1, 12V_JACK1.2, 12V_JACK1.3, BTN_APU1.3, BTN_APU2.3, BTN_APU_AGENT1.3, BTN_APU_TEST1.2, BTN_ENG1_AGENT1.3, BTN_ENG1_AGENT2.3, BTN_ENG1_TEST1.2, BTN_ENG2_AGENT1.3, BTN_ENG2_AGENT2.3, BTN_ENG2_TEST1.2, BTN_ENG11.3, BTN_ENG12.3, BTN_ENG21.3, BTN_ENG22.3, C1.2, C2.2, C3.2, R1.2, R2.2, R3.2, U1.1 (GND), U2.1 (GND), U3.1 (GND), U4.3 (GND), U4.4 (GND), U4.23 (GND)
unnamed: APU1.1 (K), APU2.2 (A)
unnamed: APU2.1 (K), APU3.2 (A)
unnamed: APU3.1 (K), APU4.2 (A)
unnamed: APU5.1 (K), APU6.2 (A)
unnamed: APU6.1 (K), APU7.2 (A)
unnamed: APU7.1 (K), APU8.2 (A)
unnamed: BL_1.1 (K), BL_2.2 (A)
unnamed: BL_2.1 (K), BL_3.2 (A)
unnamed: BL_3.1 (K), BL_4.2 (A)
unnamed: BL_5.1 (K), BL_6.2 (A)
unnamed: BL_6.1 (K), BL_7.2 (A)
unnamed: BL_7.1 (K), BL_8.2 (A)
unnamed: BL_9.1 (K), BL_10.2 (A)
unnamed: BL_10.1 (K), BL_11.2 (A)
unnamed: BL_11.1 (K), BL_12.2 (A)
unnamed: BL_13.1 (K), BL_14.2 (A)
unnamed: BL_14.1 (K), BL_15.2 (A)
unnamed: BL_15.1 (K), BL_16.2 (A)
unnamed: BL_17.1 (K), BL_18.2 (A)
unnamed: BL_18.1 (K), BL_19.2 (A)
unnamed: BL_19.1 (K), BL_20.2 (A)
unnamed: BL_21.1 (K), BL_22.2 (A)
unnamed: BL_22.1 (K), BL_23.2 (A)
unnamed: BL_23.1 (K), BL_24.2 (A)
unnamed: ENG11.1 (K), ENG12.2 (A)
unnamed: ENG12.1 (K), ENG13.2 (A)
unnamed: ENG13.1 (K), ENG14.2 (A)
unnamed: ENG15.1 (K), ENG16.2 (A)
unnamed: ENG16.1 (K), ENG17.2 (A)
unnamed: ENG17.1 (K), ENG18.2 (A)
unnamed: ENG21.1 (K), ENG22.2 (A)
unnamed: ENG22.1 (K), ENG23.2 (A)
unnamed: ENG23.1 (K), ENG24.2 (A)
unnamed: ENG25.1 (K), ENG26.2 (A)
unnamed: ENG26.1 (K), ENG27.2 (A)
unnamed: ENG27.1 (K), ENG28.2 (A)
unnamed: R1.1, U1.15 (R-EXT)
unnamed: R2.1, U2.15 (R-EXT)
unnamed: R3.1, U3.15 (R-EXT)
OSH_CLOCK: U1.3 (CLK), U2.3 (CLK), U3.3 (CLK), U4.2 (D0/RX)
OSH_DATA: U1.2 (SDI), U4.5 (D2)
OSH_DOUT1: U1.14 (SDO), U2.2 (SDI)
OSH_DOUT2: U2.14 (SDO), U3.2 (SDI)
OSH_LATCH: U1.4 (LE(ED1)), U2.4 (LE(ED1)), U3.4 (LE(ED1)), U4.1 (D1/TX)
OUT_BRT_BACK: U3.13 (~OE(ED2)), U4.13 (~D10/A10)
OUT_BRT_LED: U1.13 (~OE(ED2)), U2.13 (~OE(ED2)), U4.6 (~D3)

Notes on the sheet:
Arduino
Button Lights
Buttons
Korry
Backlighting
External Power (12V)
Lighting Korrys
Lighting Control
Integral lighting behind the front panel
Backlight

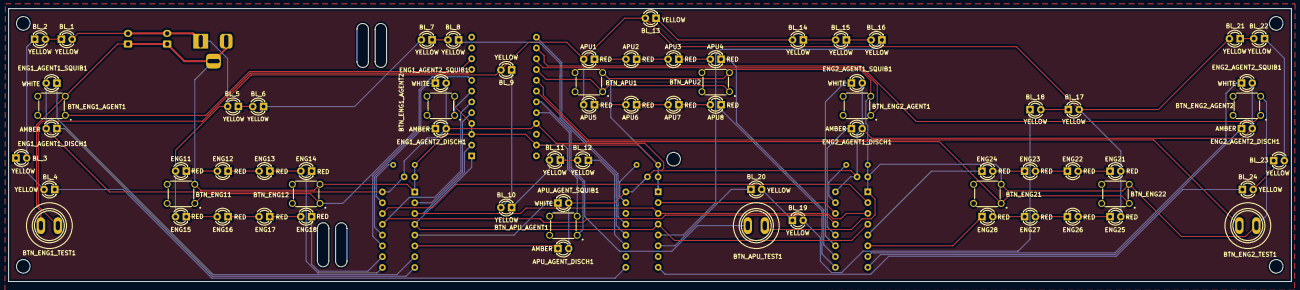
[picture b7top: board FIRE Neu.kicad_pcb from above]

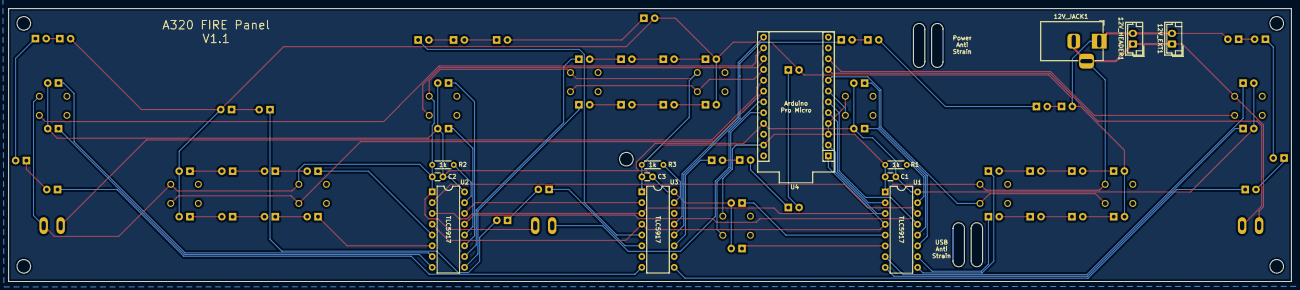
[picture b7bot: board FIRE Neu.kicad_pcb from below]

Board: 2 copper layers, 302.0 x 64.2 mm, 85 parts (13 on the bottom side), 82 nets.
